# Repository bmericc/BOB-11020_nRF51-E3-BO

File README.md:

View this project on [CADLAB.io](https://cadlab.io/node/798). 

## E3-nRf51-BO

This is a breakout board for the popular inexpensive nRF51822 modules with 
dual 2x9 1.27 mm pin headers.

This product is jointly developed by [Explore Embedded][1] and [electronut.in][2].

[1]: https://www.exploreembedded.com/
[2]: http://electronut.in/

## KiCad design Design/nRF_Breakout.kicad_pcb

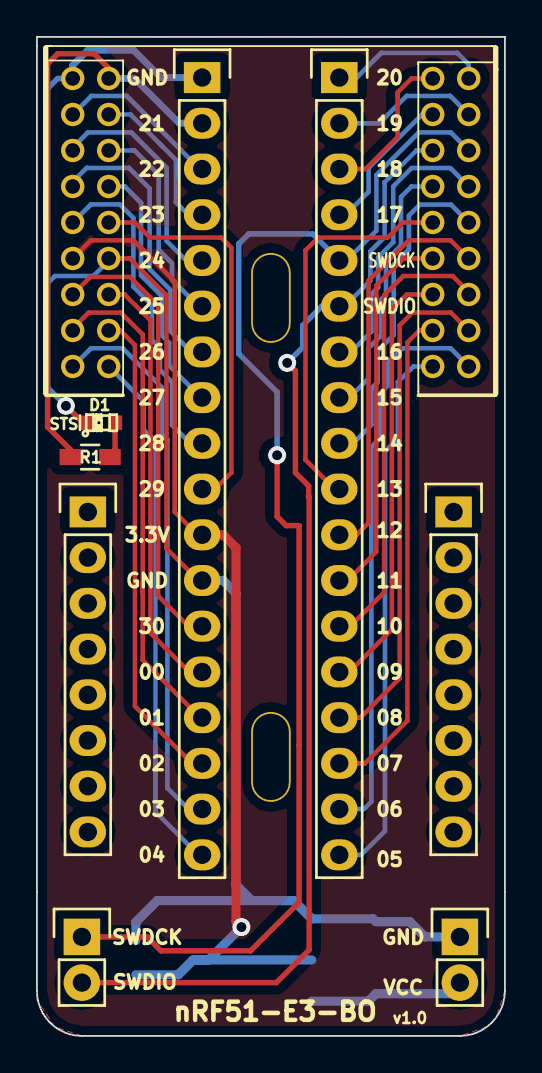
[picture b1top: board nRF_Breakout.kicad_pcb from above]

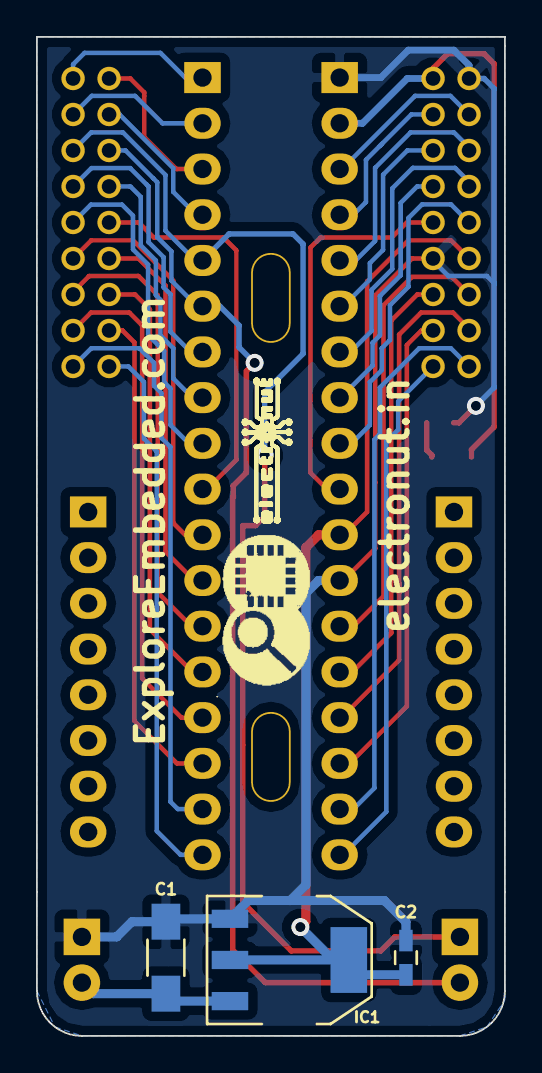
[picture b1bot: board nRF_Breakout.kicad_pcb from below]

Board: 2 copper layers, 26.0 x 55.5 mm, 16 parts (5 on the bottom side), 37 nets.

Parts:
C1: 10uF; C_1206_HandSoldering
C2: 0.1uF; C_0603_HandSoldering
D1: LED; LED-0603_NEW
IC1: LM1117; LM_1117
LOGO: LOGO (2)
P1, P3: CONN_01X18; Pin_Header_Straight_1x18
P2, P5: CONN_01X08; Pin_Header_Straight_1x08
P4, P6: CONN_01X02; Pin_Header_Straight_1x02
P7, P8: CONN_01X01; 1pin
R1: 470r; R_0603_HandSoldering
U1: nRF51822; nRF81522Final
U$2: LOGO; LOGO_electronut

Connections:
GND: C1.2, C2.2, D1.2, IC1.1, P1.1, P1.12, P4.1, U1.1, U1.12
unnamed: C1.1, IC1.3, P4.2
unnamed: C2.1, IC1.2, IC1.4, P1.11, U1.11
unnamed: D1.1, R1.2
unnamed: P1.2, R1.1, U1.2
unnamed: P1.3, U1.3
unnamed: P1.4, U1.4
unnamed: P1.5, U1.5
unnamed: P1.6, U1.6
unnamed: P1.7, U1.7
unnamed: P1.8, U1.8
unnamed: P1.9, U1.9
unnamed: P1.10, U1.10
unnamed: P1.13, U1.13
unnamed: P1.14, U1.14
unnamed: P1.15, U1.15
unnamed: P1.16, U1.16
unnamed: P1.17, U1.17
unnamed: P1.18, U1.18
unnamed: P3.1, U1.36
unnamed: P3.2, U1.34
unnamed: P3.3, U1.35
unnamed: P3.4, U1.33
unnamed: P3.5, P6.1, U1.32
unnamed: P3.6, P6.2, U1.31
unnamed: P3.7, U1.30
unnamed: P3.8, U1.29
unnamed: P3.9, U1.28
unnamed: P3.10, U1.27
unnamed: P3.11, U1.26
unnamed: P3.12, U1.25
unnamed: P3.13, U1.24
unnamed: P3.14, U1.23
unnamed: P3.15, U1.22
unnamed: P3.16, U1.21
unnamed: P3.17, U1.20
unnamed: P3.18, U1.19

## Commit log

2015-08-13 Added Files
2015-08-18 ADDED NEW FILES
2015-08-19 Corrected File
2015-08-19 corrected files
2015-08-20 added logo
2015-09-07 Changed name
2015-09-08 added README
2015-09-08 added README with images
2015-09-08 removed EAGLE files
2015-09-09 added board name and version
2015-09-09 Final
2017-06-24 gerber
2018-03-27 Backlink to CADLAB.io has been added.
